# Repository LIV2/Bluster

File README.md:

# Bluster - A2000 CPLD Buster replacment
This is a replacement for the Buster IC used in the Amiga 2000

## Programming the CPLD
Download the firmware corresponding to your board revision (right-click -> save as):

* [Rev A](https://github.com/LIV2/Bluster/raw/master/Binary/Bluster_rev_a.jed)
* [Rev B](https://github.com/LIV2/Bluster/raw/master/Binary/Bluster_rev_b.jed)
* [Rev C](https://github.com/LIV2/Bluster/raw/master/Binary/Bluster_rev_c.jed)

And follow the instructions found [Here](Programming.md)

## Revision History
So far there are no functional differences across the various revisions, just rerouting, pin swapping and part changes
 
* Rev A: Initial Revision
* Rev B: Design into smaller PCB
* Rev C: Tweak PCB design, change LDO to more standard LM1117 type

## Bill of materials
Make sure to use the BOM that matches the revision of your Bluster PCB.

* [Rev A/B BOM](BOM_rev_ab.md)
* [Rev C BOM](BOM_rev_c.md)

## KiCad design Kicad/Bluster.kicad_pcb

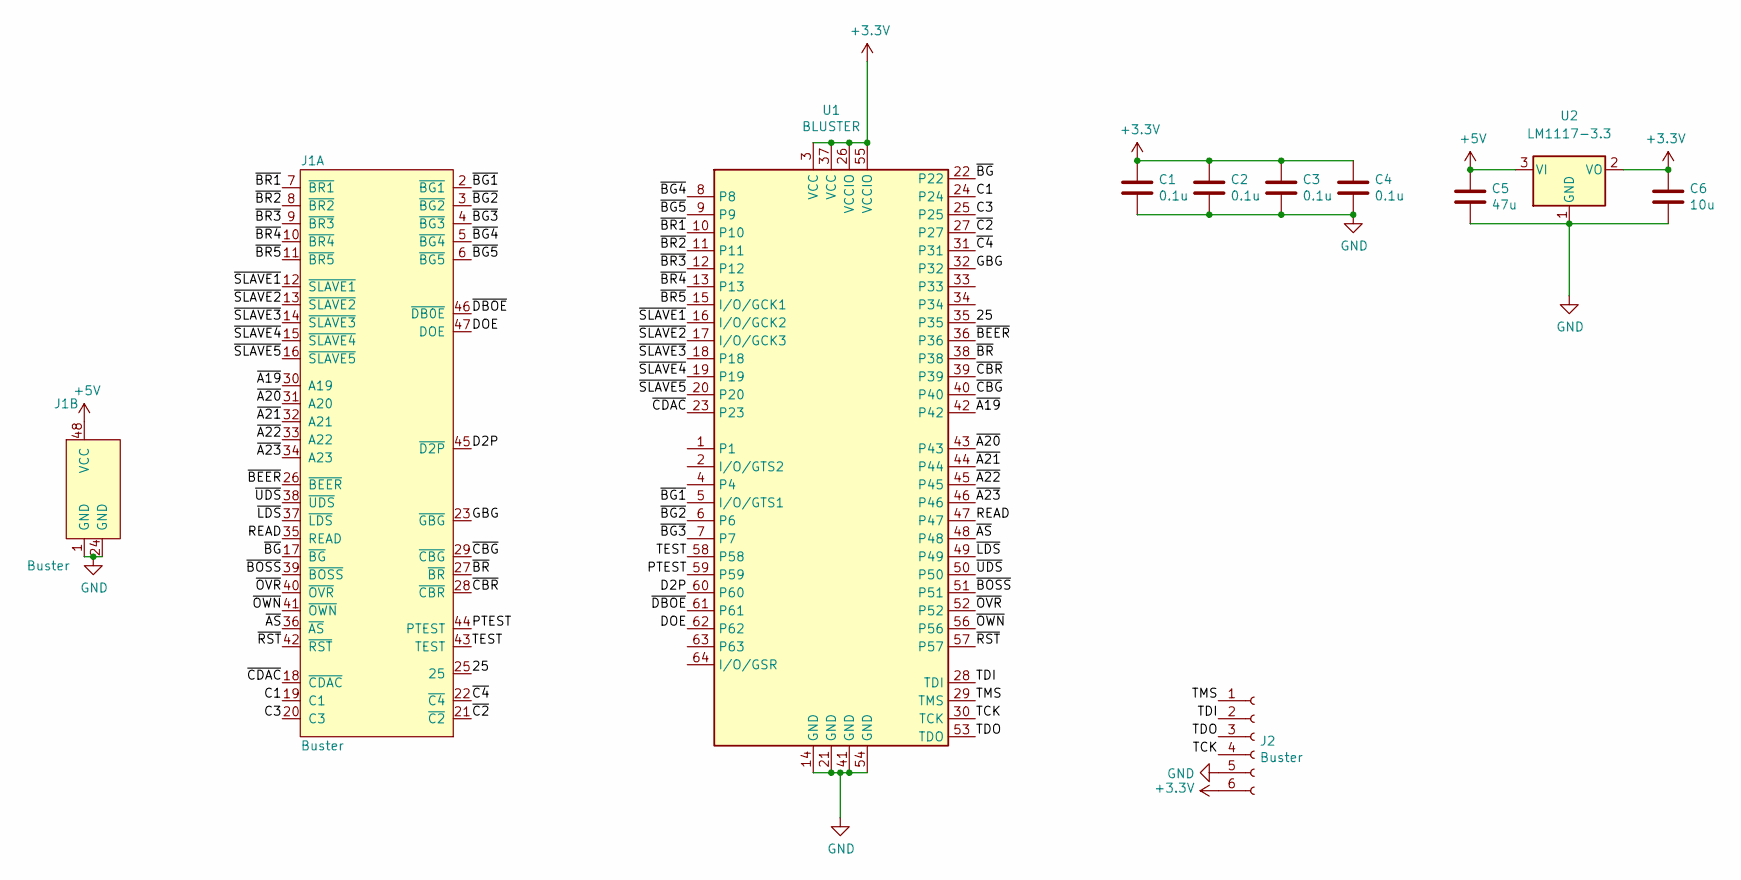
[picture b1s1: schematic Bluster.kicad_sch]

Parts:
C1, C2, C3, C4: 0.1u; C_0805_2012Metric_Pad1.18x1.45mm_HandSolder
C5: 47u; C_0805_2012Metric_Pad1.18x1.45mm_HandSolder
C6: 10u; C_0805_2012Metric_Pad1.18x1.45mm_HandSolder
J1: Buster; DIP-48_W15.24mm_Socket
J2: Buster; PinHeader_1x06_P2.54mm_Vertical
U1: BLUSTER; TQFP-64_10x10mm_P0.5mm
U2: LM1117-3.3; SOT-223-3_TabPin2

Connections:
+3V3: C1.1, C2.1, C3.1, C4.1, C6.1, J2.6, U1.3 (VCC), U1.26 (VCCIO), U1.37 (VCC), U1.55 (VCCIO), U2.2 (VO)
+5V: C5.1, J1.48 (VCC), U2.3 (VI)
/25: J1.25, U1.35
/C1: J1.19 (C1), U1.24
/C3: J1.20 (C3), U1.25
/D2P: J1.45 (~D2P), U1.60
/DOE: J1.47 (DOE), U1.62
/GBG: J1.23 (~GBG), U1.32
/PTEST: J1.44 (PTEST), U1.59
/READ: J1.35 (READ), U1.47
/TCK: J2.4, U1.30 (TCK)
/TDI: J2.2, U1.28 (TDI)
/TDO: J2.3, U1.53 (TDO)
/TEST: J1.43 (TEST), U1.58
/TMS: J2.1, U1.29 (TMS)
/~A19: J1.30 (A19), U1.42
/~A20: J1.31 (A20), U1.43
/~A21: J1.32 (A21), U1.44
/~A22: J1.33 (A22), U1.45
/~A23: J1.34 (A23), U1.46
/~AS: J1.36 (~AS), U1.48
/~BEER: J1.26 (~BEER), U1.36
/~BG1: J1.2 (~BG1), U1.5 (I/O/GTS1)
/~BG2: J1.3 (~BG2), U1.6
/~BG3: J1.4 (~BG3), U1.7
/~BG4: J1.5 (~BG4), U1.8
/~BG5: J1.6 (~BG5), U1.9
/~BG: J1.17 (~BG), U1.22
/~BOSS: J1.39 (~BOSS), U1.51
/~BR1: J1.7 (~BR1), U1.10
/~BR2: J1.8 (~BR2), U1.11
/~BR3: J1.9 (~BR3), U1.12
/~BR4: J1.10 (~BR4), U1.13
/~BR5: J1.11 (~BR5), U1.15 (I/O/GCK1)
/~BR: J1.27 (~BR), U1.38
/~C2: J1.21 (~C2), U1.27
/~C4: J1.22 (~C4), U1.31
/~CBG: J1.29 (~CBG), U1.40
/~CBR: J1.28 (~CBR), U1.39
/~CDAC: J1.18 (~CDAC), U1.23
/~DBOE: J1.46 (~DB0E), U1.61
/~LDS: J1.37 (~LDS), U1.49
/~OVR: J1.40 (~OVR), U1.52
/~OWN: J1.41 (~OWN), U1.56
/~RST: J1.42 (~RST), U1.57
/~SLAVE1: J1.12 (~SLAVE1), U1.16 (I/O/GCK2)
/~SLAVE2: J1.13 (~SLAVE2), U1.17 (I/O/GCK3)
/~SLAVE3: J1.14 (~SLAVE3), U1.18
/~SLAVE4: J1.15 (~SLAVE4), U1.19
/~SLAVE5: J1.16 (~SLAVE5), U1.20
/~UDS: J1.38 (~UDS), U1.50
GND: C1.2, C2.2, C3.2, C4.2, C5.2, C6.2, J1.1 (GND), J1.24 (GND), J2.5, U1.14 (GND), U1.21 (GND), U1.41 (GND), U1.54 (GND), U2.1 (GND)

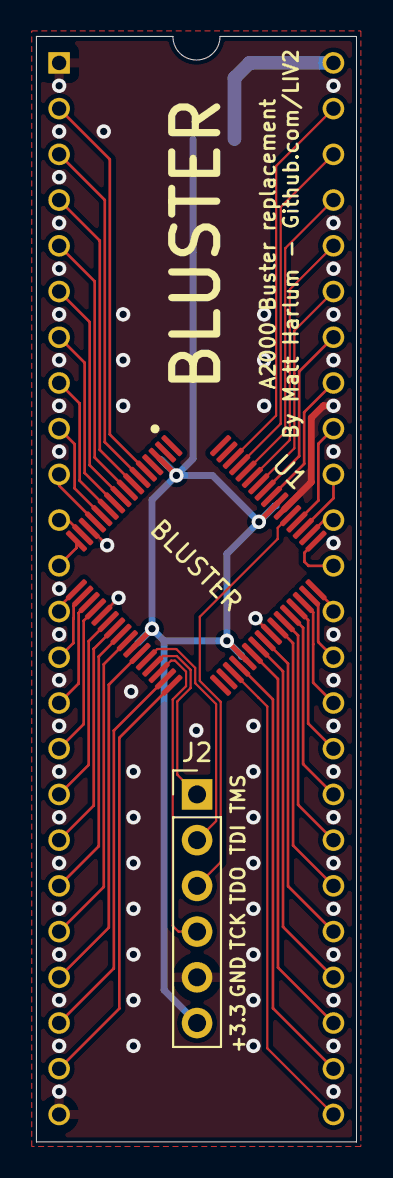
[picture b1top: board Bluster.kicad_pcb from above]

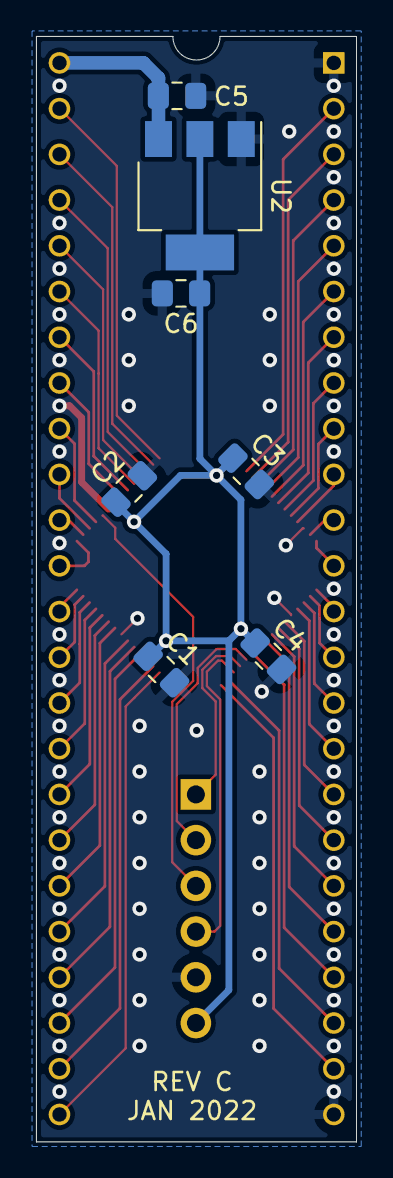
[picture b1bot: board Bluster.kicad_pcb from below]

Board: 2 copper layers, 17.8 x 61.4 mm, 10 parts (7 on the bottom side), 52 nets.

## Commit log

2021-02-13 Initial commit.
2021-03-27 Add CPLD Programming instructions
2021-07-14 Add makefile stuff
2021-07-15 Fixup makefile flashing
2021-10-06 Re-do PCB to fit within standard DIP footprint
    Fixes #1
2021-10-10 It helps to update the schematic...
2021-11-06 Add -L option to curl command
2022-01-02 Tweak DBOE/DOE timings to try and match the timings of a real buster
    * Delay DBOE/DOE slightly
    * Change compile time option "slew" to slow fixing a DBOE glitch
2022-01-16 Rev C
    * Change LDO to LM1117
    * Route extra pins to allow use for Gary
2022-01-16 Add Rev C jed
2022-01-16 Add revision history to Readme
2022-03-06 It helps to publish the gerbers...
2022-03-06 It helps to regenerate gerbers...
2022-03-26 Fixup TDI trace which stuck out to the side of the pad
2022-06-10 Fix-up incorrect Gerbers in repo
2022-12-02 Add link to boms based on REV
2022-12-05 Fixup Makefile prerequisites for rev_c
2023-01-23 Update BOMs, C5 can be 10uF to simplify the BOM
2023-01-26 Regenerate Rev_C JED
    Not sure what was wrong with it, but it wasn't working...
2023-02-02 Update comments for bus grant circuit
2024-02-10 Update BOM_rev_c.md
    Corrected the quantity for the 10uF cap in the rev C BOM
2024-02-19 mainboard collision:
    Fix comment for Chip ram to reflect correct range
    Fix RESERVED - Should be B80000-BFFFFF not A00000-BFFFFF
    Related to Issue #11
2024-02-19 Fixup collision logic
    XORing multiple inputs just tells us if there's an even number of slaves active, not if there's more than 1.
    Changed this logic so that it correctly marks a collision if there is more than one PIC or Mainboard space access at the same time
    This relates to issue #11
2026-01-15 Add diego build
2026-01-15 Add diego binary
2026-01-16 Fixup CBR
